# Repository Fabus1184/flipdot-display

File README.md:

# flipdot-display

A flipdot panel driven by an ESP32. This repository includes the driver board (KiCad) and the firmware (Rust).

## Repository layout

| Path                               | What                                                                                                                                                      |
| ---------------------------------- | --------------------------------------------------------------------------------------------------------------------------------------------------------- |
| [`firmware/`](firmware/)           | ESP32 firmware (Rust, `esp-hal`, bare metal)                                                                                                              |
| [`firmware/core/`](firmware/core/) | The firmware's hardware-independent part: panel driver with its safety rules, frame buffer, font, screen layout, clock discipline, parsing of network replies. A separate crate so it can be unit-tested on the PC. |
| [`hardware/`](hardware/)           | Driver board in KiCad 10: schematics, PCB, libraries, fabrication export, pinout, errata                                                                  |

## How it works

### The dots

Each [flipdot](https://en.wikipedia.org/wiki/Flip-disc_display) is a
magnetised disc on a coil. A current pulse flips it, the direction of the
current picks the colour, and the disc stays put without power.

The panel wires its 28 × 16 coils as a matrix. Each coil sits between its
column and the midpoint of two diodes, which connect to the row's two lines,
B and A. So current flows either from B through the coil into the column, or
from the column through the coil into A: one path per colour. An
[FP2800A](https://reaktor23.org/projects/flipdot/fp2800-datasheet.pdf) on the
panel connects the selected column to +HV or GND.

### The driver board

The board switches the rows and powers the panel:

- **High side:** an [AO3401A](https://www.lcsc.com/product-detail/C15127.html)
  connects `ROWnB` to +HV, its gate driven by a
  [ULN2803A](https://www.ti.com/lit/ds/symlink/uln2803a.pdf).
- **Low side:** an [AO3400A](https://www.lcsc.com/product-detail/C20917.html)
  connects `ROWnA` to GND.
- Four [74HC595](https://assets.nexperia.com/documents/data-sheet/74HC_HCT595.pdf)
  hold the 32 switch enables. An
  [XL6019](https://www.lcsc.com/datasheet/lcsc_datasheet_2309151739_XLSEMI-XL6019E1_C73018.pdf)
  boost converter makes +HV (16–25 V) from USB-C.

| High side, one row | Low side, one row |
| --- | --- |
|  |  |

### Flipping one dot

1. Latch one row switch into the shift registers (`HSS_EN_r` for one colour,
   `LSS_EN_r` for the other) and enable it with `SR_OE#`.
2. Point the FP2800A at the column with the opposite polarity and pulse
   `FP_EN` for 500 µs.
3. Switch everything off and wait 500 µs.

Never more than one row switch is on, or the FP2800A would be overloaded; the
firmware enforces and tests this ([one dot at a time](firmware/README.md#one-dot-at-a-time)).
Schematics, pinout and errata are in [`hardware/`](hardware/).

## Firmware

Rust on `esp-hal`, bare metal. Core 0 drives the panel and pulses only the dots
that change (1 ms each, so a full redraw takes 0.5 s). Core 1 runs WiFi and a
status page at `http://<board-ip>/`. What the panel shows is up to the
application; [`firmware/README.md`](firmware/README.md) describes the included
one and its settings.

Install the toolchain once:

```bash
cargo install espup espflash && espup install
```

Copy the config and fill in WiFi and the application settings:

```bash
cp firmware/config.example.toml firmware/config.toml
```

Build, flash and open the serial monitor:

```bash
source ~/export-esp.sh && cargo flash
```

| Command (top-level directory) | What |
| --- | --- |
| `cargo test`, `cargo clippy` | Host tests and lints of `firmware/core` |
| `cargo firmware`, `cargo firmware-clippy` | Build or lint the ESP32 image |
| `hardware/export.sh` | ERC, DRC, schematic parity, then PDF, BOM and Gerbers |

CI runs all of these.

## License

[CC BY-NC-SA 4.0](LICENSE): you may use, change and share everything in this
repository (firmware, hardware, documentation) for non-commercial purposes, as
long as you credit this project and share changes under the same license.
Commercial use is not allowed.

The symbols and footprints from LCSC/EasyEDA in the KiCad libraries, and the
KiCad stock symbols `TestPoint` and `PWR_FLAG`, keep their original licenses.

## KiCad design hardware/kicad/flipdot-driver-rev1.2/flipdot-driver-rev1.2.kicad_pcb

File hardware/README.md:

# Hardware

*KiCad render of the assembled board, including the parts JLCPCB does not
assemble: electrolytics, toroid, trimmer, headers and the ESP32 DevKit in its
sockets. USB-C and the 50-pin ribbon cable to the panel are plugged in.*

| Assembled, top | Bare board, top | Bare board, bottom |
| --- | --- | --- |
|  |  |  |

The panel is a 28 × 16 flipdot module. It carries the FP2800A column driver
and the dot coils with their diodes. The driver board here does the rest:

- row drivers for all 16 rows, in both directions;
- a socket for an ESP32 DevKit;
- a USB-C input with a boost converter for the coil voltage.

All design files are **KiCad 10** projects:

| Project | What | Status |
| --- | --- | --- |
| [`kicad/flipdot-driver/`](kicad/flipdot-driver/) | Driver board **Rev 2.1** (SMD), 100 × 85 mm, 2 layers | Current. First ordered from JLCPCB in June 2026. |
| [`kicad/flipdot-driver-rev1.2/`](kicad/flipdot-driver-rev1.2/) | Driver board **Rev 1.2** (through-hole), 140 × 71 mm | Superseded, kept for reference |
| [`kicad/panel-wiring/`](kicad/panel-wiring/) | Drawing of the panel's connector and coil/diode matrix | Documentation only, not a circuit |
| [`kicad/figures/`](kicad/figures/) | The README figures: coil matrix with current paths, block diagram | Documentation only |

Each project brings its own symbol and footprint library (`flipdot.kicad_sym`,
`flipdot.pretty/`), so it opens without extra library setup.

The projects were converted from EasyEDA Pro on 2026-11-25 (see
[History](#history)). KiCad is the source of truth from now on.

## Rev 2.1 at a glance

The top sheet has these blocks:

- **Rows.** There are 16 high-side and 16 low-side switches, one pair per row.
  Each switch type is drawn once as a sub-sheet ([`hss.kicad_sch`](kicad/flipdot-driver/hss.kicad_sch),
  [`lss.kicad_sch`](kicad/flipdot-driver/lss.kicad_sch)) and placed 16 times
  (`HS row 0…15`, `LS row 0…15`). Every placement has its own component
  references.
  - The **high-side** switches use an AO3401A P-MOSFET with a 10 V Zener gate
    clamp. Two ULN2803A arrays pull their gates.
  - The **low-side** switches use an AO3400A N-MOSFET.
- **Control.** Four 74HC595 shift registers hold one enable bit per row and
  switch direction (`HSS_EN_n`, `LSS_EN_n`). The ULN2803A outputs that drive
  the high-side gates are `HSD0`–`HSD15`.
- **Columns.** The FP2800A on the panel drives the columns. It is wired
  straight from the ESP32 through the 2 × 25 panel header H1.
- **Power.**
  - USB-C supplies 5 V. D21 is the TVS diode.
  - The XL6019 boost converter (U12) makes the coil voltage **+HV**. The
    feedback divider R102 + R105 / R103 sets it to about 16–25 V, adjustable
    with R105.
  - The `BOOST_EN` jumper (H2) enables the converter.
- **[ESP32 sheet](kicad/flipdot-driver/esp32.kicad_sch).** This sheet holds the
  ESP32 DevKit socket (U5) and the test pads TP1–TP9.
  - The socket has two header pairs per side, so it takes both narrow and wide
    30-pin DevKits.
  - The DevKit plugs in. It is not soldered, so it is not in the BOM.

| High-side switch (one channel) | Low-side switch (one channel) |
| --- | --- |
|  |  |

### ESP32 pinout

These GPIOs are on the Rev 2.1 silkscreen and are used by the firmware
([`firmware/src/main.rs`](../firmware/src/main.rs)):

| Signal | Net | GPIO |
| --- | --- | --- |
| Shift register clock | `SR_ICLK` | 15 |
| Shift register latch | `SR_OCLK` | 2 |
| Shift register data | `SR_DATA` | 4 |
| Shift register output enable (active low) | `SR_OE#` | 16 |
| FP2800A enable | `FP_EN` | 13 |
| FP2800A data (polarity) | `FP_DATA` | 12 |
| FP2800A address A0, A1, A2 | `FP_A0`–`FP_A2` | 14, 27, 26 |
| FP2800A address B0, B1 | `FP_B0`, `FP_B1` | 25, 33 |

Rev 1.2 uses the same GPIOs.

GPIO12, GPIO2 and GPIO15 are **strapping pins**. GPIO12 must be low at reset,
because high selects 1.8 V flash and the module will not boot. GPIO2 must be
low or floating to enter the serial bootloader.

## Errata of the first Rev 2.1 boards

The boards ordered in June 2026 were made from the EasyEDA layout (document
"PCB8", silkscreen "rev. n+1"). The KiCad files fix the first two items below
and drop a company logo. The silkscreen now reads "rev. 2.1", "USB SIDE
HERE" and "WIFI SIDE HERE" (DevKit orientation, German on the first boards)
and "POWER" at the LED.

1. **Known defect: the low-side MOSFET sources are not connected to GND.**
   - **What is wrong.** On these boards, the sources of Q1–Q16 and the low
     ends of their gate pull-downs sit on two isolated nets: EasyEDA's
     `$1N37900` and `$1N38170`. They belong on the real ground. Without it, the
     low-side switches cannot sink coil current.
   - **Cause.** The GND symbols for these nets were missing from the schematic
     when the PCB was laid out and ordered on 2026-06-04
     (`PCB8_20260604114714`). They were added to the schematic on 2026-06-20.
   - **Fix for an affected board.** Wire both nets to GND: pad 1 of R80 (Q1–Q7, Q14)
     and pad 1 of R5 (Q8–Q13, Q15, Q16).
   - **KiCad PCB.** Fixed: both nets are GND and connect through the ground
     pours. A board made from the KiCad files does not need the wire.
2. **USB-C shield.** On these boards the USB-C shell pads (USB1 pins 13, 14) have no
   net, while the schematic ties them to GND. The KiCad PCB follows the
   schematic.
3. **C6 / C12 value.** These capacitors are labelled 470 µF, but their LCSC
   part `UVR1H101MPD1TD` is a 100 µF / 50 V capacitor. Check what is fitted
   before reordering.

## Checks and outputs

```bash
hardware/export.sh
```

The script runs on `flipdot-driver` by default. Pass `flipdot-driver-rev1.2`
for the old board.

First it runs the checks, and it stops if one fails:

- ERC with no findings.
- DRC with no unconnected items.
- No schematic/PCB parity issues.

Then it writes these files to `kicad/<project>/output/` (git-ignored):

- the schematic as a PDF;
- the BOM with MPN and LCSC numbers;
- Gerbers and Excellon drill files as a zip;
- the placement file.

CI runs the same script, see the `hardware` job in
[`.github/workflows/ci.yml`](../.github/workflows/ci.yml).

**Known DRC findings, all on the board as manufactured:**

| Board | Silkscreen (overlap with copper/silk/edge) | Other |
| --- | --- | --- |
| Rev 2.1 | 55 | 9 edge clearances inside the LCSC USB-C footprint (its slot is 0.16 mm from the pads), 4 courtyard overlaps |
| Rev 1.2 | 175 | – |

The routing uses EasyEDA's 4 mil (0.1 mm) clearance. The net classes keep that
value, so the existing tracks pass.

**3D models.** Most parts use KiCad's official 3D library
(`${KICAD10_3DMODEL_DIR}`). It ships with KiCad's 3D package; on Arch that is
`kicad-library-3d`. Two models have no public equivalent and are bundled in
`kicad/flipdot-driver/flipdot.3dshapes/`: the toroid inductor and the ESP32
DevKit. See [`tools/3d-models/`](tools/3d-models/) for how they were placed and
which parts are approximations. Rev 1.2 has no 3D models.

The assembled renders above use a detailed third-party DevKit model and 3M's
model of the 50-pin ribbon plug (3425-6650); the cables were modelled only for
the render. None of these are in this repository, so in KiCad you see the
simplified bundled DevKit and no cables.

## History

The board was designed in EasyEDA Pro and converted to KiCad on 2026-11-25.
The original EasyEDA project is not published. KiCad cannot read its `.epro2`
format, so the
[migration tools](tools/easyeda-migration/) convert it in three steps:

1. Turn it into the older `.epro` format.
2. Run KiCad's own importer on that file.
3. Rebuild what the importer cannot do:
   - the hierarchical sheets;
   - the bus lines;
   - the DevKit socket and test pads, which were EasyEDA free pads;
   - the mounting holes;
   - the net names;
   - the links between PCB and schematic.

A re-run reproduces the same netlists.

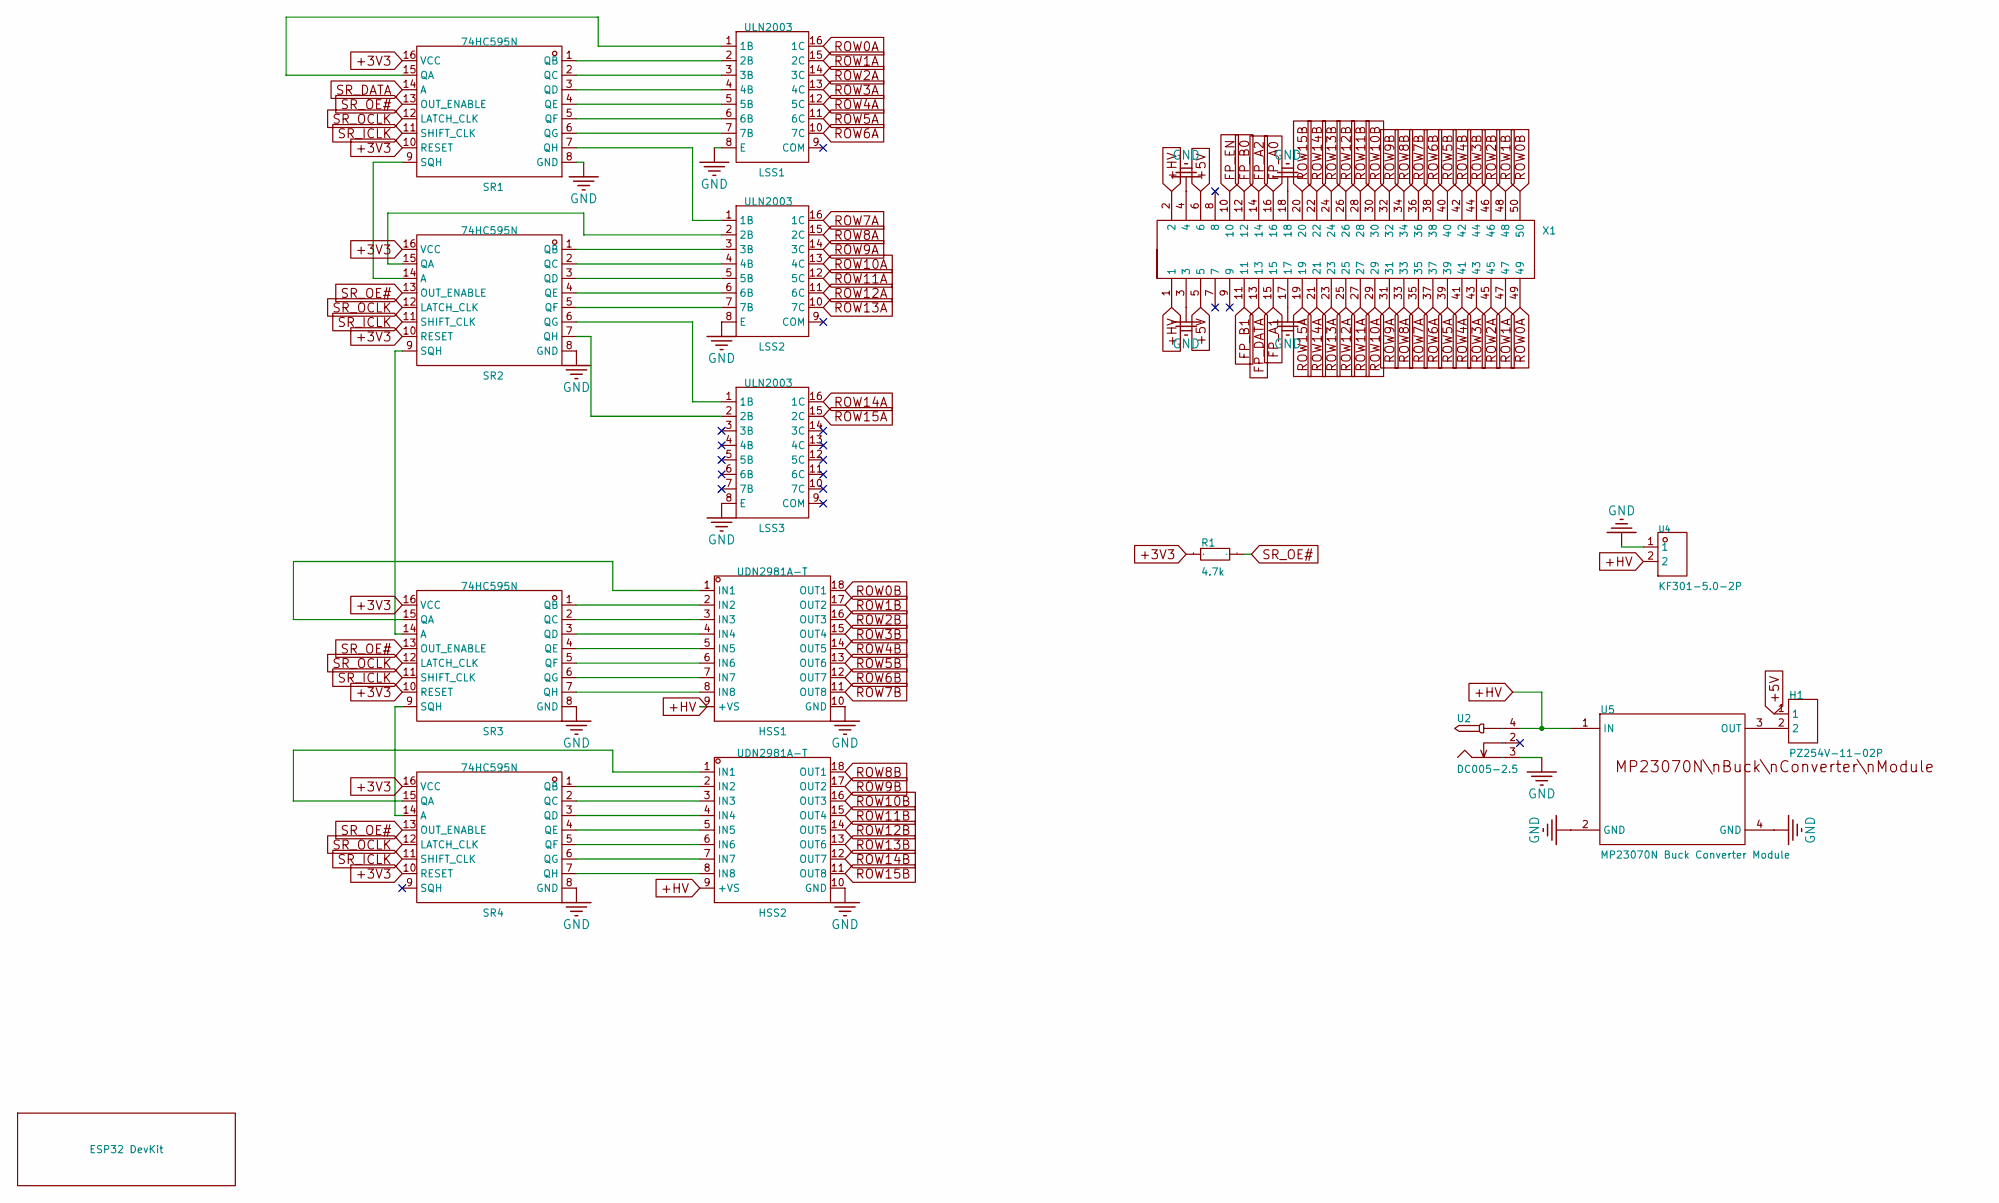
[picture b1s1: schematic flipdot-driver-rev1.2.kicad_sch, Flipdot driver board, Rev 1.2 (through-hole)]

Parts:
H1: PZ254V-11-02P; HDR-TH_2P-P2.54-V-M; Manufacturer Part PZ254V-11-02P; LCSC Part Name 1x2P 间距:2.54mm 方针 直插
HSS1, HSS2: UDN2981A-T; DIP-18_L23.0-W6.5-P2.54-LS7.6-BL; Manufacturer Part UDN2981A-T; LCSC Part Name UDN2981A-T
LSS1, LSS2, LSS3: ULN2003; DIP-16_L19.8-W6.5-P2.54-LS7.6-BL; Manufacturer Part ULN2003; LCSC Part Name ULN2003
R1: 4.7k; RES-TH_BD2.4-L6.3-P10.30-D0.6; Manufacturer Part MFR-25FTF52-4K7; LCSC Part Name 金属膜电阻 4.7kΩ ±1% 250mW
SR1, SR2, SR3, SR4: 74HC595N; DIP-16_L19.8-W6.5-P2.54-LS7.6-BL; Manufacturer Part 74HC595N; LCSC Part Name 74HC595N 停产
U2: DC005-2.5; DC-IN-TH_DC005-2.5MM; Manufacturer Part DC005-2.5; LCSC Part Name DC电源插座 内径:2.5mm 外径:6.3mm
U4: KF301-5.0-2P; CONN-TH_P5.00_KF301-5.0-2P; Manufacturer Part KF301-5.0-2P; LCSC Part Name 5mm 1x2P 排数:1 每排P数:2 直插
U5: MP23070N Buck Converter Module; MP23070N BUCK CONVERTER MODULE; Manufacturer Part MP23070N Buck Converter Module
X1: IDC-TH_50P-P2.54_BOOMELE2X25P; Manufacturer Part 2.54-2*25P简牛; LCSC Part Name 2.54mm 2x25P 排数:2 每排P数:25

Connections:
+3V3: R1.1, SR1.10 (RESET), SR1.16 (VCC), SR2.10 (RESET), SR2.16 (VCC), SR3.10 (RESET), SR3.16 (VCC), SR4.10 (RESET), SR4.16 (VCC); also elsewhere on the board
+5V: H1.1, X1.5, X1.6; also elsewhere on the board
+HV: HSS1.9 (+VS), HSS2.9 (+VS), U2.4, U4.2, U5.1 (IN), X1.1, X1.2
FP_A0: X1.16; also elsewhere on the board
FP_A1: X1.15; also elsewhere on the board
FP_A2: X1.14; also elsewhere on the board
FP_B0: X1.12; also elsewhere on the board
FP_B1: X1.11; also elsewhere on the board
FP_DATA: X1.13; also elsewhere on the board
FP_EN: X1.10; also elsewhere on the board
GND: HSS1.10 (GND), HSS2.10 (GND), LSS1.8 (E), LSS2.8 (E), LSS3.8 (E), SR1.8 (GND), SR2.8 (GND), SR3.8 (GND), SR4.8 (GND), U2.3, U4.1, U5.2 (GND), U5.4 (GND), X1.3, X1.4, X1.17, X1.18; also elsewhere on the board
unnamed: HSS1.1 (IN1), SR3.15 (QA)
unnamed: HSS1.2 (IN2), SR3.1 (QB)
unnamed: HSS1.3 (IN3), SR3.2 (QC)
unnamed: HSS1.4 (IN4), SR3.3 (QD)
unnamed: HSS1.5 (IN5), SR3.4 (QE)
unnamed: HSS1.6 (IN6), SR3.5 (QF)
unnamed: HSS1.7 (IN7), SR3.6 (QG)
unnamed: HSS1.8 (IN8), SR3.7 (QH)
unnamed: HSS2.1 (IN1), SR4.15 (QA)
unnamed: HSS2.2 (IN2), SR4.1 (QB)
unnamed: HSS2.3 (IN3), SR4.2 (QC)
unnamed: HSS2.4 (IN4), SR4.3 (QD)
unnamed: HSS2.5 (IN5), SR4.4 (QE)
unnamed: HSS2.6 (IN6), SR4.5 (QF)
unnamed: HSS2.7 (IN7), SR4.6 (QG)
unnamed: HSS2.8 (IN8), SR4.7 (QH)
unnamed: LSS1.1 (1B), SR1.15 (QA)
unnamed: LSS1.2 (2B), SR1.1 (QB)
unnamed: LSS1.3 (3B), SR1.2 (QC)
unnamed: LSS1.4 (4B), SR1.3 (QD)
unnamed: LSS1.5 (5B), SR1.4 (QE)
unnamed: LSS1.6 (6B), SR1.5 (QF)
unnamed: LSS1.7 (7B), SR1.6 (QG)
unnamed: LSS2.1 (1B), SR1.7 (QH)
unnamed: LSS2.2 (2B), SR2.15 (QA)
unnamed: LSS2.3 (3B), SR2.1 (QB)
unnamed: LSS2.4 (4B), SR2.2 (QC)
unnamed: LSS2.5 (5B), SR2.3 (QD)
unnamed: LSS2.6 (6B), SR2.4 (QE)
unnamed: LSS2.7 (7B), SR2.5 (QF)
unnamed: LSS3.1 (1B), SR2.6 (QG)
unnamed: LSS3.2 (2B), SR2.7 (QH)
unnamed: SR1.9 (SQH), SR2.14 (A)
unnamed: SR2.9 (SQH), SR3.14 (A)
unnamed: SR3.9 (SQH), SR4.14 (A)
unnamed: H1.2, U5.3 (OUT)
ROW0A: LSS1.16 (1C), X1.49
ROW0B: HSS1.18 (OUT1), X1.50
ROW1A: LSS1.15 (2C), X1.47
ROW1B: HSS1.17 (OUT2), X1.48
ROW2A: LSS1.14 (3C), X1.45
ROW2B: HSS1.16 (OUT3), X1.46
ROW3A: LSS1.13 (4C), X1.43
ROW3B: HSS1.15 (OUT4), X1.44
ROW4A: LSS1.12 (5C), X1.41
ROW4B: HSS1.14 (OUT5), X1.42
ROW5A: LSS1.11 (6C), X1.39
ROW5B: HSS1.13 (OUT6), X1.40
ROW6A: LSS1.10 (7C), X1.37
ROW6B: HSS1.12 (OUT7), X1.38
ROW7A: LSS2.16 (1C), X1.35
ROW7B: HSS1.11 (OUT8), X1.36
ROW8A: LSS2.15 (2C), X1.33
ROW8B: HSS2.18 (OUT1), X1.34
ROW9A: LSS2.14 (3C), X1.31
ROW9B: HSS2.17 (OUT2), X1.32
ROW10A: LSS2.13 (4C), X1.29
ROW10B: HSS2.16 (OUT3), X1.30
ROW11A: LSS2.12 (5C), X1.27
ROW11B: HSS2.15 (OUT4), X1.28
ROW12A: LSS2.11 (6C), X1.25
ROW12B: HSS2.14 (OUT5), X1.26
ROW13A: LSS2.10 (7C), X1.23
ROW13B: HSS2.13 (OUT6), X1.24
ROW14A: LSS3.16 (1C), X1.21
ROW14B: HSS2.12 (OUT7), X1.22
ROW15A: LSS3.15 (2C), X1.19
ROW15B: HSS2.11 (OUT8), X1.20
SR_DATA: SR1.14 (A); also elsewhere on the board
SR_ICLK: SR1.11 (SHIFT_CLK), SR2.11 (SHIFT_CLK), SR3.11 (SHIFT_CLK), SR4.11 (SHIFT_CLK); also elsewhere on the board
SR_OCLK: SR1.12 (LATCH_CLK), SR2.12 (LATCH_CLK), SR3.12 (LATCH_CLK), SR4.12 (LATCH_CLK); also elsewhere on the board
SR_OE#: R1.2, SR1.13 (OUT_ENABLE), SR2.13 (OUT_ENABLE), SR3.13 (OUT_ENABLE), SR4.13 (OUT_ENABLE); also elsewhere on the board

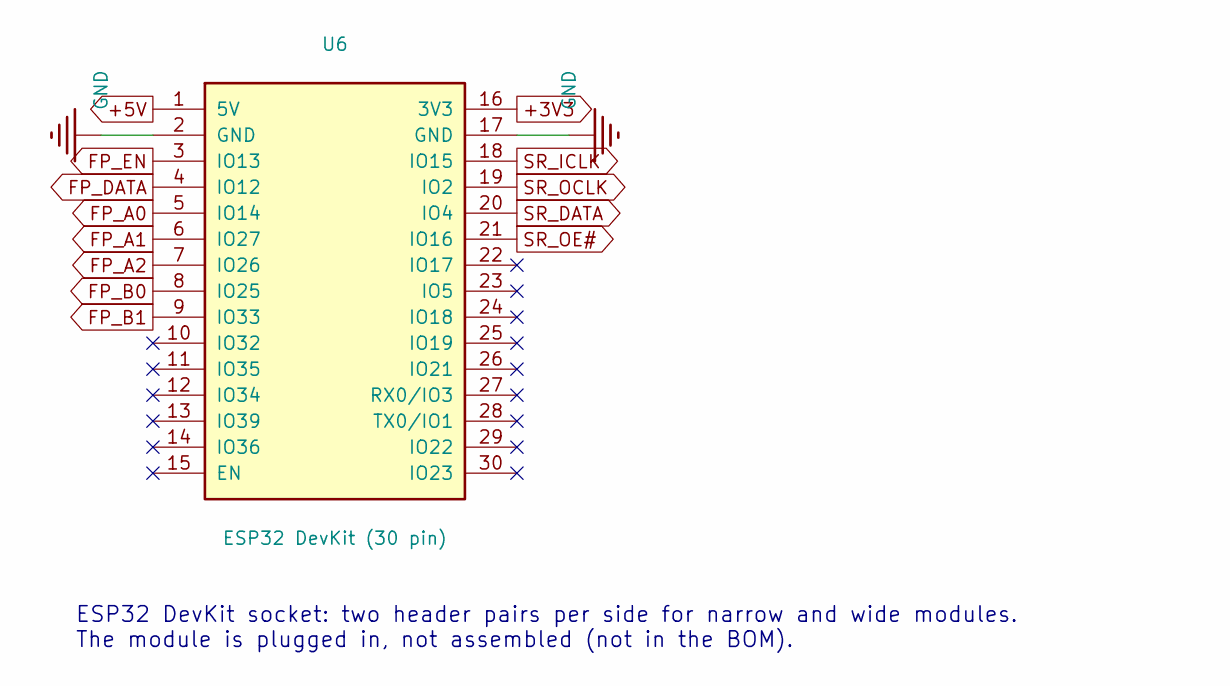
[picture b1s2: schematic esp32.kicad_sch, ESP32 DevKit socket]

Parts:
U6: ESP32 DevKit (30 pin); ESP32_DevKit_30pin_2widths

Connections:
+3V3: U6.16 (3V3); also elsewhere on the board
+5V: U6.1 (5V); also elsewhere on the board
FP_A0: U6.5 (IO14); also elsewhere on the board
FP_A1: U6.6 (IO27); also elsewhere on the board
FP_A2: U6.7 (IO26); also elsewhere on the board
FP_B0: U6.8 (IO25); also elsewhere on the board
FP_B1: U6.9 (IO33); also elsewhere on the board
FP_DATA: U6.4 (IO12); also elsewhere on the board
FP_EN: U6.3 (IO13); also elsewhere on the board
GND: U6.2 (GND), U6.17 (GND); also elsewhere on the board
SR_DATA: U6.20 (IO4); also elsewhere on the board
SR_ICLK: U6.18 (IO15); also elsewhere on the board
SR_OCLK: U6.19 (IO2); also elsewhere on the board
SR_OE#: U6.21 (IO16); also elsewhere on the board

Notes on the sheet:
ESP32 DevKit socket: two header pairs per side for narrow and wide modules. The module is plugged in, not assembled (not in the BOM).

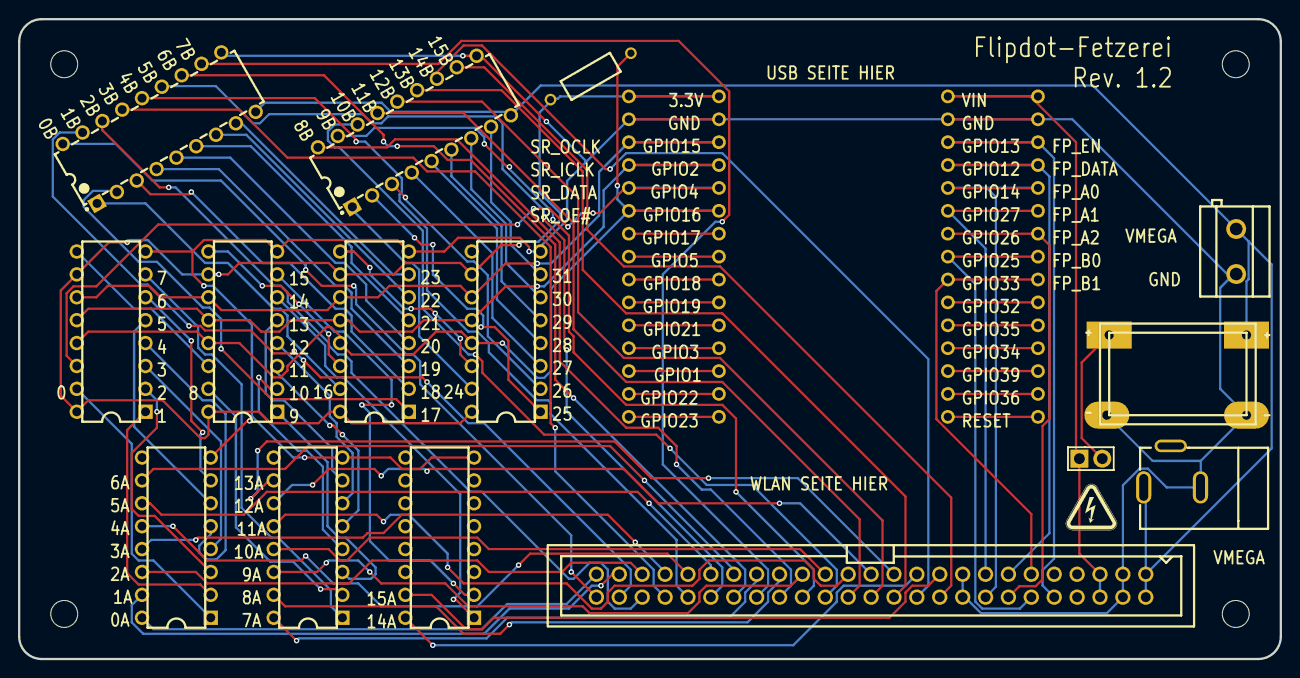
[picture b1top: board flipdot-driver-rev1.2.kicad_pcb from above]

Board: 2 copper layers, 140.0 x 71.0 mm, 20 parts (0 on the bottom side), 83 nets.

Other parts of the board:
MH1, MH2, MH3, MH4: MountingHole; MountingHole_3.0mm

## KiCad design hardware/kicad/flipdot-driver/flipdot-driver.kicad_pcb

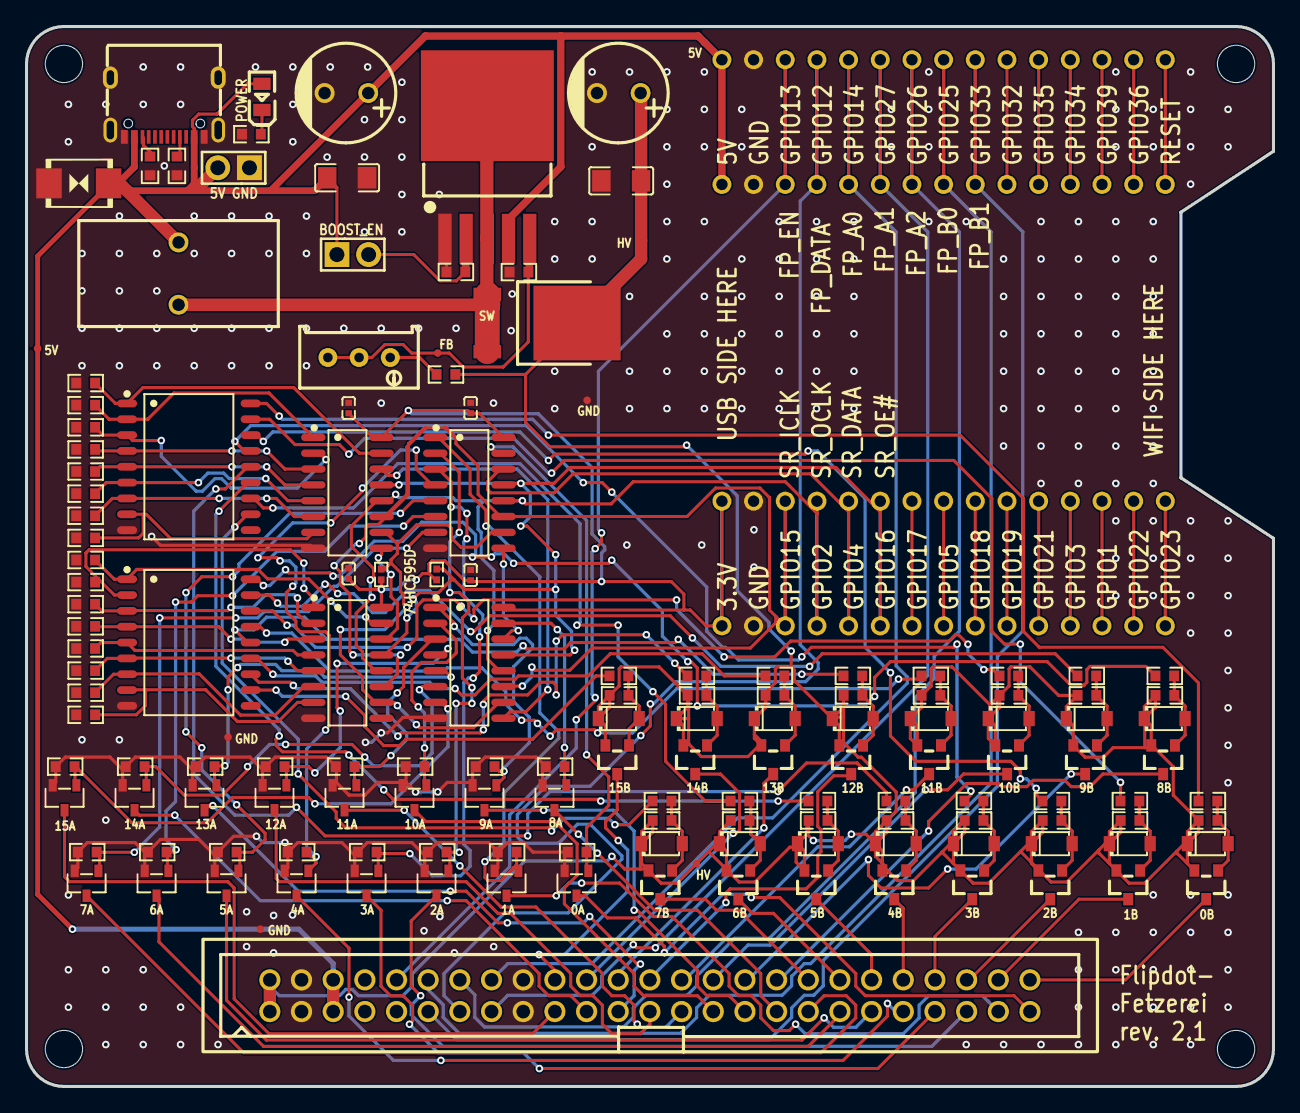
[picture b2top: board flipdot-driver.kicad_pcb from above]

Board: 2 copper layers, 100.0 x 85.0 mm, 158 parts (0 on the bottom side), 122 nets.

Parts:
C4, C11: 10uF; C1206
C6, C12: 470uF; CAP-TH_BD8.0-P3.50-D0.6-FD
C7, C8, C9, C10: 100nF; C0402
D1, D2, D3, D4, D5, D6, D7, D8, D9, D10, D11, D12, D13, D14, D15, D16: BZT52C10; SOD-123_L2.7-W1.6-LS3.7-RD
D21: P6SMB6.8CA/TR13; SMB_L4.6-W3.6-LS5.3-BI
D23: MBRD1045; TO-252-3_L6.5-W5.9-P4.60-LS10.0-BL
H1: IDC-TH_50P-P2.54_BOOMELE2X25P
H2, H3: PZ254V-11-02P; HDR-TH_2P-P2.54-V-M
L1: 47uH; IND-TH_L16.0-W8.5-P5.00-D0.7
LED2: KT-0805G; LED0805-R-RD
MH1, MH2, MH3, MH4: MountingHole; MountingHole_3.0mm
Q1, Q2, Q3, Q4, Q5, Q6, Q7, Q8, Q9, Q10, Q11, Q12, Q13, Q14, Q15, Q16: AO3400A; SOT-23-3_L2.9-W1.3-P1.90-LS2.4-BR
Q17, Q18, Q19, Q20, Q21, Q22, Q23, Q24, Q25, Q26, Q27, Q28, Q29, Q30, Q31, Q32: AO3401A; SOT-23_L2.9-W1.3-P1.90-LS2.4-BR
R1, R20, R21, R22, R23, R24, R25, R26, R27, R28, R29, R30, R31, R32, R33, R34, R35, R36, R37, R38, R39, R40, R41, R42, R43, R44, R45, R46, R47, R48, R49, R50: 1k; R0603
R2, R14: 4.7k; R0402
R3, R4, R5, R6, R7, R8, R9, R10, R11, R12, R13, R15, R16, R17, R18, R19, R71, R72, R73, R74, R76, R77, R78, R79, R80, R81, R82, R83, R84, R85, R86, R87: 10k; R0603
R60: 470R; R0603
R61, R98: 5.1k; R0603
R102: 18k; R0603
R103: 1.5k; R0603
R104: 100k; R0603
R105: 10k; RES-ADJ-TH_3P-L10.0-W10.0-P2.50-L
TP1, TP4: +5V; TestPoint_Pad_D0.6mm
TP2: SW; TestPoint_Pad_D0.6mm
TP3, TP9: +HV; TestPoint_Pad_D0.6mm
TP5: FB; TestPoint_Pad_D0.6mm
TP6, TP7, TP8: GND; TestPoint_Pad_D0.6mm
U1, U2, U3, U4: 74HC595D,118; SOIC-16_L9.9-W3.9-P1.27-LS6.0-BL
U5: ESP32 DevKit (30 pin); ESP32_DevKit_30pin_2widths
U8, U9: ULN2803A; SOP-18_L11.4-W7.6-P1.27-LS10.6-BL
U12: XL6019E1; TO-263-5_L10.2-W9.9-P1.70-LS14.4-TL
USB1: TYPE-C 16PIN 2MD(073); USB-C-SMD_TYPE-C-6PIN-2MD-073

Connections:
+3V3: C7.2, C8.2, C9.2, C10.2, R2.1, R14.1, U1.16, U2.16, U3.16, U4.16, U5.16
+5V: C11.2, C12.1, D21.2, H1.5, H1.6, H2.1, H3.2, L1.1, LED2.1, TP1.1, TP4.1, U5.1, U12.4, USB1.2, USB1.11
+HV: C4.2, C6.1, D1.1, D2.1, D3.1, D4.1, D5.1, D6.1, D7.1, D8.1, D9.1, D10.1, D11.1, D12.1, D13.1, D14.1, D15.1, D16.1, D23.2, H1.1, H1.2, Q17.2, Q18.2, Q19.2, Q20.2, Q21.2, Q22.2, Q23.2, Q24.2, Q25.2, Q26.2, Q27.2, Q28.2, Q29.2, Q30.2, Q31.2, Q32.2, R1.2, R22.2, R24.2, R26.2, R28.2, R30.2, R32.2, R34.2, R36.2, R38.2, R40.2, R42.2, R44.2, R46.2, R48.2, R50.2, R102.2, TP3.1, TP9.1
/HSD0: R20.1, U8.18
/HSD1: R21.1, U8.17
/HSD2: R23.1, U8.16
/HSD3: R25.1, U8.15
/HSD4: R27.1, U8.14
/HSD5: R29.1, U8.13
/HSD6: R31.1, U8.12
/HSD7: R33.1, U8.11
/HSD8: R35.1, U9.18
/HSD9: R37.1, U9.17
/HSD10: R39.1, U9.16
/HSD11: R41.1, U9.15
/HSD12: R43.1, U9.14
/HSD13: R45.1, U9.13
/HSD14: R47.1, U9.12
/HSD15: R49.1, U9.11
BOOST_FB: R103.1, R105.2, R105.3, TP5.1, U12.5
BOOST_SW: D23.1, D23.3, L1.2, TP2.1, U12.3, U12.6
FP_A0: H1.16, U5.5
FP_A1: H1.15, U5.6
FP_A2: H1.14, U5.7
FP_B0: H1.12, U5.8
FP_B1: H1.11, U5.9
FP_DATA: H1.13, U5.4
FP_EN: H1.10, U5.3
GND: C4.1, C6.2, C7.1, C8.1, C9.1, C10.1, C11.1, C12.2, D21.1, H1.3, H1.4, H1.17, H1.18, H3.1, Q1.2, Q2.2, Q3.2, Q4.2, Q5.2, Q6.2, Q7.2, Q8.2, Q9.2, Q10.2, Q11.2, Q12.2, Q13.2, Q14.2, Q15.2, Q16.2, R3.1, R4.1, R5.1, R6.1, R7.1, R8.1, R9.1, R10.1, R11.1, R12.1, R13.1, R15.1, R16.1, R17.1, R18.1, R19.2, R60.1, R61.2, R71.2, R72.2, R73.2, R74.2, R76.1, R77.1, R78.1, R79.1, R80.1, R81.2, R82.2, R83.2, R84.1, R85.1, R86.1, R87.1, R98.2, R103.2, R104.1, TP6.1, TP7.1, TP8.1, U1.8, U2.8, U3.8, U4.8, U5.2, U5.17, U8.9, U9.9, U12.1, USB1.1, USB1.12, USB1.13, USB1.14
HSS_EN_0: R71.1, U3.15, U8.1
HSS_EN_1: R72.1, U3.1, U8.2
HSS_EN_2: R73.1, U3.2, U8.3
HSS_EN_3: R74.1, U3.3, U8.4
HSS_EN_4: R76.2, U3.4, U8.5
HSS_EN_5: R77.2, U3.5, U8.6
HSS_EN_6: R78.2, U3.6, U8.7
HSS_EN_7: R79.2, U3.7, U8.8
HSS_EN_8: R19.1, U4.15, U9.1
HSS_EN_9: R81.1, U4.1, U9.2
HSS_EN_10: R82.1, U4.2, U9.3
HSS_EN_11: R83.1, U4.3, U9.4
HSS_EN_12: R84.2, U4.4, U9.5
HSS_EN_13: R85.2, U4.5, U9.6
HSS_EN_14: R86.2, U4.6, U9.7
HSS_EN_15: R87.2, U4.7, U9.8
LSS_EN_0: Q1.1, R80.2, U1.15
LSS_EN_1: Q2.1, R3.2, U1.1
LSS_EN_2: Q3.1, R4.2, U1.2
LSS_EN_3: Q14.1, R10.2, U1.3
LSS_EN_4: Q4.1, R15.2, U1.4
LSS_EN_5: Q5.1, R16.2, U1.5
LSS_EN_6: Q6.1, R17.2, U1.6
LSS_EN_7: Q7.1, R18.2, U1.7
LSS_EN_8: Q8.1, R13.2, U2.15
LSS_EN_9: Q9.1, R5.2, U2.1
LSS_EN_10: Q10.1, R6.2, U2.2
LSS_EN_11: Q11.1, R7.2, U2.3
LSS_EN_12: Q12.1, R8.2, U2.4
LSS_EN_13: Q13.1, R9.2, U2.5
LSS_EN_14: Q15.1, R11.2, U2.6
LSS_EN_15: Q16.1, R12.2, U2.7
unnamed: D1.2, Q17.1, R1.1, R20.2
unnamed: D2.2, Q18.1, R21.2, R22.1
unnamed: D3.2, Q19.1, R23.2, R24.1
unnamed: D4.2, Q20.1, R25.2, R26.1
unnamed: D5.2, Q21.1, R27.2, R28.1
unnamed: D6.2, Q22.1, R29.2, R30.1
unnamed: D7.2, Q23.1, R31.2, R32.1
unnamed: D8.2, Q24.1, R33.2, R34.1
unnamed: D9.2, Q25.1, R35.2, R36.1
unnamed: D10.2, Q26.1, R37.2, R38.1
unnamed: D11.2, Q27.1, R39.2, R40.1
unnamed: D12.2, Q28.1, R41.2, R42.1
unnamed: D13.2, Q29.1, R43.2, R44.1
unnamed: D14.2, Q30.1, R45.2, R46.1
unnamed: D15.2, Q31.1, R47.2, R48.1
unnamed: D16.2, Q32.1, R49.2, R50.1
unnamed: LED2.2, R60.2
unnamed: R102.1, R105.1
unnamed: U1.9, U2.14
unnamed: U2.9, U3.14
unnamed: U3.9, U4.14
unnamed: H2.2, R104.2, U12.2
unnamed: R98.1, USB1.4
unnamed: R61.1, USB1.10
ROW0A: H1.49, Q1.3
ROW0B: H1.50, Q17.3
ROW1A: H1.47, Q2.3
ROW1B: H1.48, Q18.3
ROW2A: H1.45, Q3.3
ROW2B: H1.46, Q19.3
ROW3A: H1.43, Q14.3
ROW3B: H1.44, Q20.3
ROW4A: H1.41, Q4.3
ROW4B: H1.42, Q21.3
ROW5A: H1.39, Q5.3
ROW5B: H1.40, Q22.3
ROW6A: H1.37, Q6.3
ROW6B: H1.38, Q23.3
ROW7A: H1.35, Q7.3
ROW7B: H1.36, Q24.3
ROW8A: H1.33, Q8.3
ROW8B: H1.34, Q25.3
ROW9A: H1.31, Q9.3
ROW9B: H1.32, Q26.3
ROW10A: H1.29, Q10.3
ROW10B: H1.30, Q27.3
ROW11A: H1.27, Q11.3
ROW11B: H1.28, Q28.3
ROW12A: H1.25, Q12.3
ROW12B: H1.26, Q29.3
ROW13A: H1.23, Q13.3
ROW13B: H1.24, Q30.3
ROW14A: H1.21, Q15.3
ROW14B: H1.22, Q31.3
ROW15A: H1.19, Q16.3
ROW15B: H1.20, Q32.3
SR_DATA: U1.14, U5.20
SR_ICLK: U1.11, U2.11, U3.11, U4.11, U5.18
SR_MR#: R2.2, U1.10, U2.10, U3.10, U4.10
SR_OCLK: U1.12, U2.12, U3.12, U4.12, U5.19
SR_OE#: R14.2, U1.13, U2.13, U3.13, U4.13, U5.21

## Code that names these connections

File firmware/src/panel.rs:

//! The panel's GPIOs. The flip sequence and its safety rules live in
//! [`flipdot_core::panel`]; this file only connects them to the ESP32 pins.

use esp_hal::gpio::{AnyPin, Level, Output, OutputConfig, Pin as _};
use esp_hal::peripherals;
use esp_hal::time::{Duration, Instant};
pub use flipdot_core::panel::Panel;
use flipdot_core::panel::PanelPins;

/// Pin assignment, see hardware/README.md.
pub struct Pins {
    pub sr_shift_clock: AnyPin<'static>,     // SR_ICLK, GPIO15
    pub sr_latch_clock: AnyPin<'static>,     // SR_OCLK, GPIO2
    pub sr_data: AnyPin<'static>,            // SR_DATA, GPIO4
    pub sr_output_enable_n: AnyPin<'static>, // SR_OE#, GPIO16
    pub fp_enable: AnyPin<'static>,          // FP_EN, GPIO13
    pub fp_data: AnyPin<'static>,            // FP_DATA, GPIO12
    pub fp_address: [AnyPin<'static>; 5],    // FP_A0..A2, FP_B0..B1
}

pub struct EspPins {
    sr_shift_clock: Output<'static>,
    sr_latch_clock: Output<'static>,
    sr_data: Output<'static>,
    sr_output_enable_n: Output<'static>,
    fp_enable: Output<'static>,
    fp_data: Output<'static>,
    fp_address: [Output<'static>; 5],
}

fn output(pin: AnyPin<'static>, level: Level) -> Output<'static> {
    Output::new(pin, level, OutputConfig::default())
}

impl EspPins {
    /// Configures the pins. `SR_OE#` starts high and `FP_EN` low, so nothing
    /// is switched on between reset and [`Panel::new`].
    pub fn new(p: Pins) -> Self {
        Self {
            sr_output_enable_n: output(p.sr_output_enable_n, Level::High),
            fp_enable: output(p.fp_enable, Level::Low),
            sr_shift_clock: output(p.sr_shift_clock, Level::Low),
            sr_latch_clock: output(p.sr_latch_clock, Level::Low),
            sr_data: output(p.sr_data, Level::Low),
            fp_data: output(p.fp_data, Level::Low),
            fp_address: p.fp_address.map(|pin| output(pin, Level::Low)),
        }
    }
}

fn busy_wait(us: u32) {
    let start = Instant::now();
    let duration = Duration::from_micros(us as u64);
    while start.elapsed() < duration {}
}

impl PanelPins for EspPins {
    fn sr_data(&mut self, high: bool) {
        self.sr_data.set_level(Level::from(high));
    }
    fn sr_shift_clock(&mut self, high: bool) {
        self.sr_shift_clock.set_level(Level::from(high));
    }
    fn sr_latch_clock(&mut self, high: bool) {
        self.sr_latch_clock.set_level(Level::from(high));
    }
    fn sr_output_enable_n(&mut self, high: bool) {
        self.sr_output_enable_n.set_level(Level::from(high));
    }
    fn fp_enable(&mut self, high: bool) {
        self.fp_enable.set_level(Level::from(high));
    }
    fn fp_data(&mut self, high: bool) {
        self.fp_data.set_level(Level::from(high));
    }
    fn fp_address(&mut self, address: u8) {
        for (bit, pin) in self.fp_address.iter_mut().enumerate() {
            pin.set_level(Level::from(address >> bit & 1 == 1));
        }
    }
    fn delay_us(&mut self, us: u32) {
        busy_wait(us);
    }
    fn uninterrupted(&mut self, f: impl FnOnce(&mut Self)) {
        // Masks interrupts on this core only. A critical section would also
        // take the lock the other core needs, stalling the network for the
        // whole pulse.
        esp_hal::xtensa_lx::interrupt::free(|| f(self));
    }
}

/// Switches the column driver and all row switches off, whatever owns the
/// pins. For the panic handler: a panic in the middle of a pulse must not
/// leave a coil powered.
pub fn emergency_off() {
    // SAFETY: only called on the way to a reset. The pins are reconfigured as
    // outputs driving their safe levels. If the other core is still running
    // the display, it keeps driving them too; each of its pulses is still a
    // single, checked dot, and a cut pulse does no harm.
    // (Output has no Drop: the pins keep driving these levels.)
    unsafe {
        Output::new(
            peripherals::GPIO13::steal().degrade(),
            Level::Low,
            OutputConfig::default(),
        );
        Output::new(
            peripherals::GPIO16::steal().degrade(),
            Level::High,
            OutputConfig::default(),
        );
    }
}

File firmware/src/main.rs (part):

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    let mut panel = panel::Panel::new(panel::EspPins::new(panel::Pins {
        sr_shift_clock: peripherals.GPIO15.degrade(),
        sr_latch_clock: peripherals.GPIO2.degrade(),
        sr_data: peripherals.GPIO4.degrade(),
        sr_output_enable_n: peripherals.GPIO16.degrade(),
        fp_enable: peripherals.GPIO13.degrade(),
        fp_data: peripherals.GPIO12.degrade(),
        fp_address: [
            peripherals.GPIO14.degrade(), // FP_A0
            peripherals.GPIO27.degrade(), // FP_A1
            peripherals.GPIO26.degrade(), // FP_A2
            peripherals.GPIO25.degrade(), // FP_B0
            peripherals.GPIO33.degrade(), // FP_B1
        ],
    }));

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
